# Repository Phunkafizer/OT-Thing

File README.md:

# OTthing

**A compact WiFi <-> OpenTherm (master & slave) interface**

## Project homepage

https://www.seegel-systeme.de/2025/01/05/ot-thing-das-universelle-wifi-opentherm-interface/

*OTthing board*

*OTthing wiring*

*OTthing web interface*

*Home Assistant integration*

## Overview

OTthing is a versatile OpenTherm gateway that connects your heating system to the Internet via WiFi. It acts as an OpenTherm master (controlling your boiler) and/or slave (integrating with room thermostats), providing real-time monitoring and control through a modern web interface and Home Assistant integration.

### Key Features

* **Dual OpenTherm Modes**: Operate as both an OpenTherm master and a slave simultaneously
* **Single-Board Compact Design**: Cost-efficient SMD-based single-board hardware with a small enclosure footprint
* **OpenTherm Compatibility**: Works with OpenTherm-compatible equipment that implements the functions supported by OTthing; available features vary by device
* **USB-C Powered**: Simple and reliable power supply through a standard USB-C connector
* **Web Dashboard**: Real-time status monitoring with system metrics
* **Home Assistant Integration**: Native MQTT discovery and seamless HA integration
* **Multi-Zone Support**: Control up to 2 heating circuits with independent parameters
* **Time Program**: Built-in scheduling for automatic heating setpoint changes
* **Heating Curve Control**: Outdoor-compensated flow temperature control with configurable curve parameters
* **Flow & Setpoint Management**: Fine-grained control for CH temperature targets, modes, and operating limits
* **Raw OpenTherm Tools**: Direct read/write request endpoint for diagnostics and advanced integrations
* **Real-Time Telemetry**: Live updates via WebSocket for logs and status changes
* **REST API**: Full HTTP interface for status, configuration, control commands, and topic discovery
* **WiFi Provisioning**: Built-in network scan and credential setup through the web interface
* **OTA Firmware Update**: In-browser firmware upload endpoint with automatic reboot on success
* **Local Data Export**: Device data and diagnostics export from the web UI for troubleshooting
* **External Inputs & Sensors**: Optional DS18B20, pulse input, or photointerrupter support (for example, condensate monitoring)
* **Selectable Operating Strategies**: Run OTthing as a full heating controller or in monitoring-first mode for telemetry-only operation
* **Automatic Bypass Behavior**: Allows you to restore conventional room-thermostat operation without rewiring
* **Failsafe Runtime Status**: Device health and communication state tracking for robust operation
* **Local Control**: Responsive web UI with no cloud dependency
* **Modular Design**: Extensible architecture supporting multiple integrations
* **Open-Source Platform**: Open hardware and firmware for custom extensions and modifications
* **Advanced Configuration**: Room modes (off/heat/auto), flow control, heating curves, and more
* **Detailed Logging**: Real-time log streaming to monitor system behavior
* **Turbo Mode**: Temporarily raises the flow target by a configurable amount and duration
* **Automatic Suspend**: Optional suspension based on outside temperature, room conditions, and minimum flow thresholds
* **Customizable dashboard**: add metrics to dashboard

## Architecture

The firmware consists of several functional modules:

* **OpenTherm Control** (`otcontrol.cpp`): Manages master/slave communication with the boiler
* **Master Requests** (`masterrequests.cpp`): Builds and schedules OpenTherm master requests and polling cycles
* **OpenTherm Values** (`otvalues.cpp`): Stores, normalizes, and exposes decoded OpenTherm data points
* **Heating Curve** (`heatingcurve.cpp`): Calculates the target flow temperature from heating-curve parameters
* **MQTT Integration** (`mqtt.cpp`): Publishes device state and subscribes to control topics
* **Device Status** (`devstatus.cpp`): Tracks runtime health, connectivity, and status flags
* **Auxiliary Input** (`auxInput.cpp`): Handles external input signals for additional control logic
* **Web Portal** (`portal.cpp`): Serves the responsive dashboard and API endpoints
* **Heating Control** (`CHcontrol.cpp`): Manages heating circuits, setpoints, and modes
* **Sensor Integration** (`sensors.cpp`): Collects data from external sensors
* **Configuration Management** (`devconfig.cpp`): Handles persistent device settings

## Hardware

* **MCU**: ESP32-C3 (or a compatible MCU with UART pins)
* **Communication**: OpenTherm interface
* **Power**: via USB
* **Optional**: DS18B20 1-Wire temperature sensors and auxiliary inputs

OpenTherm support and available controls depend on the boiler or other equipment. Check the device documentation and OTthing schematics before installation. Disconnect equipment from mains power before wiring; have boiler wiring performed by a qualified installer where required. Connect OpenTherm through the board's designated terminals, never directly to MCU GPIO pins.

## Installation & Setup

1. **Hardware Setup**:

   - Connect the OpenTherm slave side (boiler / ventilation / solar storage) to the **Boiler** screw terminal on OTthing
   - Optionally connect the room unit to the **Roomunit** screw terminals on OTthing
   - Connect OTthing to a USB-C power supply

2. **Access the Web Interface**:

   - The device creates a WiFi access point for provisioning or connects to its configured network
   - The default access point password is `12345678`; change it before deployment
   - Access the web UI at `http://<otthing-ip>/` (default: 4.3.2.1)

3. **Configure**:

   - Set your boiler type and heating circuit parameters
   - Configure the MQTT broker if you are using Home Assistant
   - Adjust setpoints, heating curves, and control modes

### Build and Flash (Developers)

Install PlatformIO, then run these commands from the `Firmware/` directory:

```bash
platformio run --environment release
platformio run --environment release --target upload
```

The first command builds the firmware. The next two upload the firmware and the LittleFS web assets; perform both uploads when installing a complete build. The firmware project reads access point SSID, password, and hostname from `default.ini` unless overridden by the build environment. Set a unique access point password before deploying devices.

## API Reference

OTthing exposes the following REST endpoints and WebSocket connection:

When web authentication is configured, protected endpoints require a valid login session. Requests without a valid session return 401; log in through the web UI before using these endpoints.

### Core Status Endpoints

* **`GET /`** - Web dashboard (HTML)
* **`GET /status`** - Current device and boiler status (JSON)
* **`GET /config`** - Device configuration and settings (JSON)
* **`POST /config`** - Update device configuration (JSON body)
* **`GET /otitems`** - Raw OpenTherm items and values from master and slave (JSON)
* **`GET /topics`** - List all available MQTT control topics (text/plain)

### Control Endpoints

* **`GET /set?key=value`** - Update settings via query parameters
  - Examples: `/set?chSetTemp1=50`, `/set?chMode1=heat`
  - Use `/topics` to discover supported control keys. URL-encode values when they contain reserved characters.
  - Returns 200 on success, 503 if the value cannot be set

* **`GET /slaverequest?id=X&rw=Y&data=HEX`** - Send a raw OpenTherm slave request
  - `id`: OpenTherm message ID (integer)
  - `rw`: 1 for READ_DATA, 0 for WRITE_DATA
  - `data`: Hex-encoded data value
  - Returns JSON with response type, ID, and data

### System Endpoints

* **`GET /scan`** - Scan for available WiFi networks
  - Returns JSON with the SSID, RSSI, and channel for each network
  - Status field: -2 (scanning in progress), -1 (failed), 0+ (number of networks found)

* **`POST /setwifi`** - Configure WiFi credentials
  - Parameters: `ssid` and `pass` (URL-encoded)
  - Triggers a device reboot and a WiFi connection attempt

* **`GET /reboot`** - Trigger a device reboot
  - Returns 200 and schedules a reboot

* **`POST /update`** - Firmware update (binary upload)
  - Returns 200 on success, 500/503 on error
  - Triggers an automatic reboot if the update succeeds

### Real-time Communication

* **`WebSocket /ws`** - Real-time updates and log streaming
  - Receives log messages and status updates
  - Can be used to monitor device behavior in real time

## Testing & Development

A Python mock server is included for local UI and API testing. Install its dependencies and start it from the `Firmware/` directory:

```bash
python -m pip install -r requirements.txt
python tools/mock_otthing.py
```

The server listens on `http://127.0.0.1:8081/`. It is useful for UI development and API integration, but it does not replace testing against physical OpenTherm hardware.

### MQTT Notes

The device subscribes to control topics under `otthing/<device-id>/<key>/set`; `/topics` lists the supported keys. Home Assistant discovery is provided through MQTT when a broker is configured.

Changes sent through the web API are also published to the corresponding MQTT `/set` topic as retained messages. A broker can replay retained commands when the device reconnects, including after a reboot. Keep this in mind for temporary controls such as Turbo mode, and clear any stale retained command from the broker when needed.

### Troubleshooting

* **Cannot reach the web UI**: Confirm the phone or computer is connected to the OTthing access point or the same network as the device, then check the device IP.
* **No OpenTherm communication**: Check the board terminals, wiring polarity where applicable, boiler compatibility, and the device's status and logs.
* **Home Assistant entities are missing**: Confirm broker connectivity and MQTT discovery settings, then review device logs and the broker's topics.
* **A setting returns 401**: Log in through the web UI and retry the request with the browser session.
* **A temporary action returns after reboot**: Check whether a retained MQTT `/set` command is replaying it.

## Schematics

## Discussion

https://community.home-assistant.io/t/ot-thing-an-opentherm-wifi-gateway-with-integrated-ot-master-slave/824667

## Reporting issues

When reporting issues, please supply:

* Brand and model of the boiler and room unit
* OTthing firmware version and the steps that reproduce the issue
* expected behaviour
* Log
* Status JSON
* Configuration JSON
* OT items JSON
* Data history JSON

All of this data can be exported from the OTthing using the export function at the bottom of the web UI.
Only one concern per issue!

## Contributing

* Make changes in a new branch based on the [`develop`](../../tree/develop) branch.
* Address only one issue per PR.
* Create the PR against the [`develop`](../../tree/develop) branch.

## Known Working Devices

Below is an excerpt of hardware devices reported to work successfully with **OTthing**. If you have verified additional devices, contributions and reports are very welcome!

### Boilers, heatpumps, heating systems, ventilation systems
* **ACV** compact HRE eco 18 solo
* **De Dietrich** Inidens 20/24 MI
* **De Dietrich** MCR 24 Home
* **De Dietrich** MPX 24/29 MI Compact
* **Domusa** BioClass HM 16 (Pellet)
* **Elco** Trigon S 
* **Hoval** TopGas
* **Ideal** Logic Max combi
* **Immergas** Victrix Tera 24 Plus
* **Intergas** Kombi Kompakt HRE 36/30 A
* **Intergas** Xtreme 36
* **Intergas** HRE 36/30A
* **Junkers** Cerasmart ZSB 3-16 *(with OpenTherm module OTM 1)*
* **Lamborghini** IX Condens 25 C
* **MHG**
* **Remeha** Elga Ace
* **Remeha** Tzerra 28c
* **Remeha** Tzerra Ace
* **Termet** Gold Plus 2
* **Viadrus** K4 (e-board SIT 7530197_01)
* **Viessmann** Vitodens 100-W (B1KG)
* **Weheat** Sparrow P60
* **Westen** Boyler Digit+
* **Windhager** BioWin (Pellet)

### Roomunits, thermostats, others
* **Baxi** RC 06.20
* **De Dietrich** AD304
* **De Dietrich** iSense (AD289)
* **Evohome** R8810 bridge
* **Google** Nest Thermostat E
* **Honeywell** DT4M
* **Hoval** RS-OT
* **Immergas** CAR V2
* **Intergas** Comfort Touch
* **Junkers** TF 30
* **MHG** Ceta 107
* **REMEHA** iSense
* **Siemens** QAA73
* **TADO** Thermostat X
* **Theben / Windhager** RAM 786

---
*Feel free to open a Pull Request or issue to report additional compatible devices!*

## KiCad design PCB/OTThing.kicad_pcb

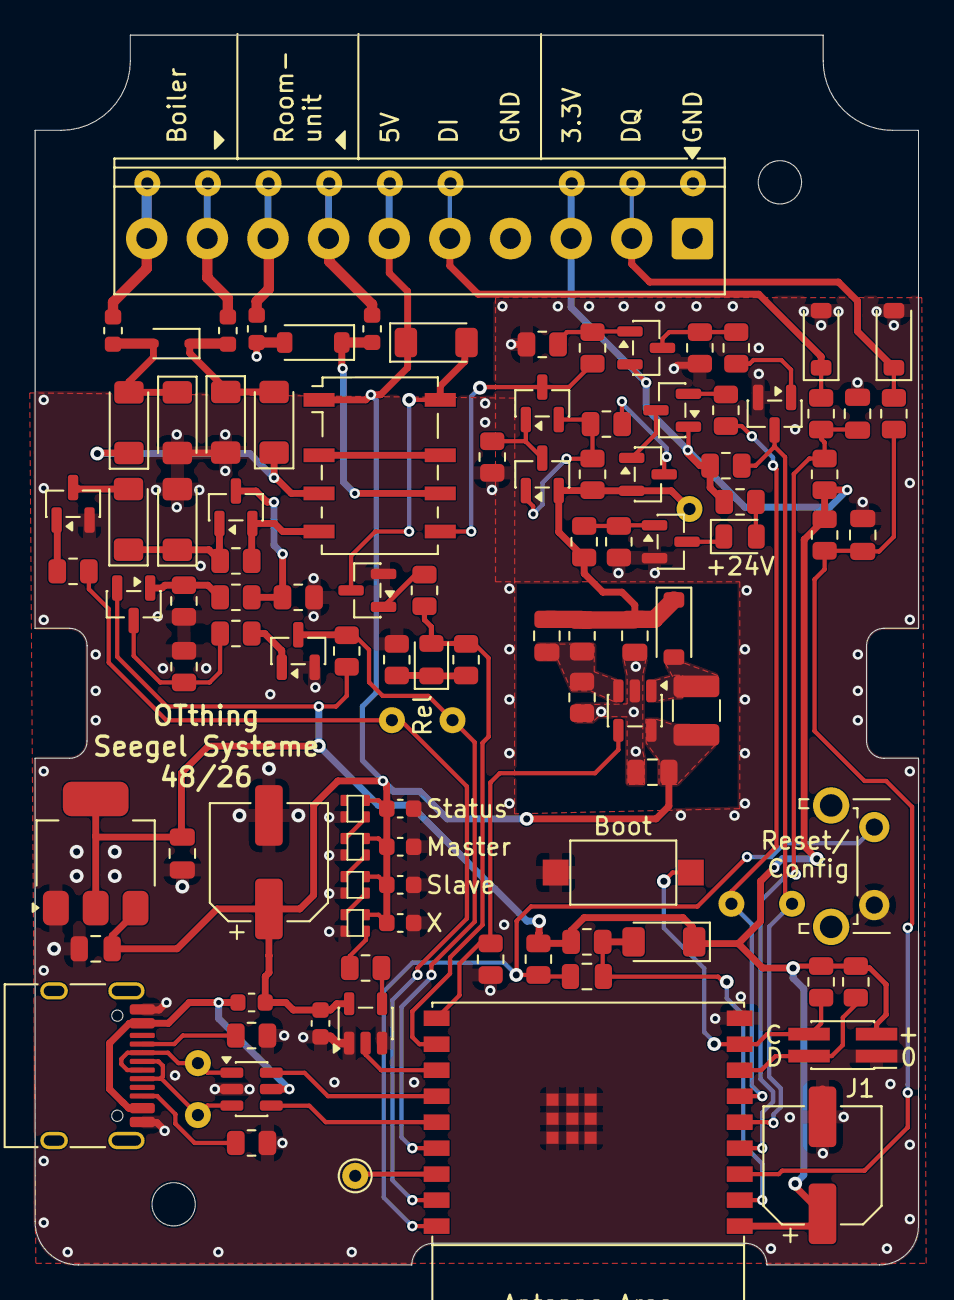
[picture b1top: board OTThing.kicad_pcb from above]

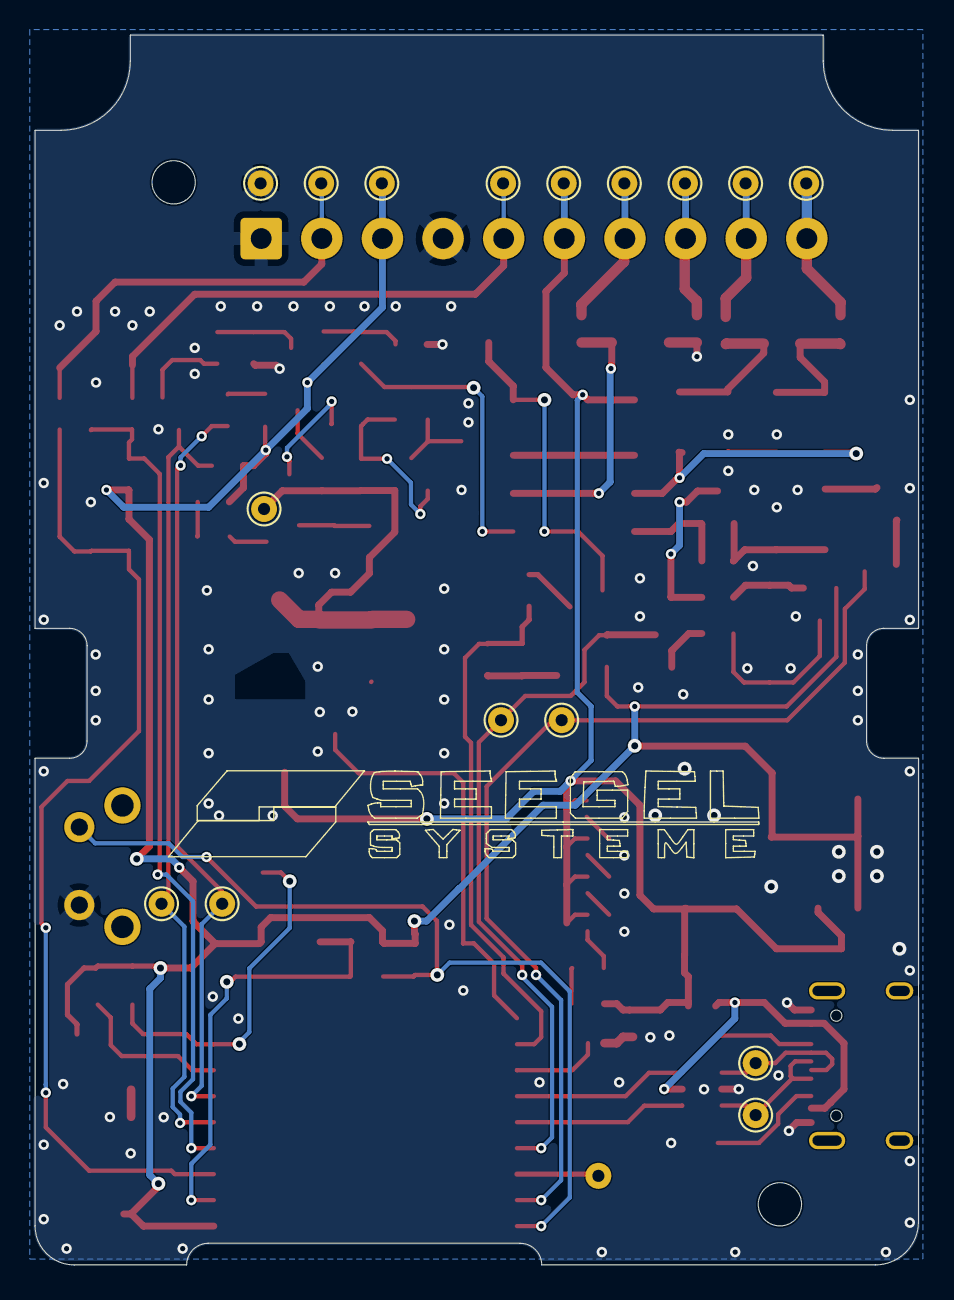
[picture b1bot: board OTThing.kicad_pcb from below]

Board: 2 copper layers, 51.0 x 71.0 mm, 119 parts (16 on the bottom side), 66 nets.

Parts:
C1, C3: 470pF; C_0805_2012Metric
C2, C4, C5: 10µ; C_0805_2012Metric
C6: 100µ; CP_Elec_6.3x5.4
C7, C9: 4µ7; C_0805_2012Metric
C8: 22pF; C_0805_2012Metric
C10: 470µ; CP_Elec_6.3x7.7
C11, C12, C13, C14, C15: 100n; C_0603_1608Metric
D1: ZMM4V3; D_MiniMELF
D2: ZMM15; D_MiniMELF
D3, D17: PTVS3V3S1UR,115; D_SOD-123
D4, D5, D6, D7, D8, D18: LL4148; D_MiniMELF
D9: MBR0540; D_SOD-123
D12, D14: YL; LED_0805_2012Metric
D15: PESD24VL1BA; D_SOD-323
D16: PTVS24VS1UR; D_SOD-123
FB1, FB2, FB3, FB4, FB5: L_0603_1608Metric
H1, H2: MountingHole; MountingHole_2.5mm
IC1: TPS61041; SOT-23-5
J1: Conn_01x04; PinHeader_2x02_P1.27mm_Vertical_SMD
J3: USB_C_Receptacle_USB2.0; USB_C_Receptacle_HRO_TYPE-C-31-M-12
J4: TerminalBlock_Phoenix_PT-1,5-10-3.5-H_1x10_P3.50mm_Horizont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
K1: G6K-2F-Y-5V; Relay_DPDT_Omron_G6K-2F-Y
L1: 10µ; L_1210_3225Metric
LED1, LED2, LED3, LED4: XL-1615RGBC-WS2812B-S
Q1, Q4, Q5, Q6, Q7, Q11: BC857C; SOT-23
Q2, Q8, Q9, Q10, Q12, Q13: BC847C; SOT-23
R1, R4, R29, R30, R31, R36, R38, R39, R40: 4k7; R_0805_2012Metric
R2, R6: 120; R_0805_2012Metric
R3: 18k; R_0805_2012Metric
R5: 470; R_0805_2012Metric
R7, R22, R33: 330; R_0805_2012Metric
R8, R9: 5k1; R_0805_2012Metric
R12, R14, R23, R26, R34: 3k3; R_0805_2012Metric
R13, R21, R27: 33k; R_0805_2012Metric
R15, R25, R28: 12k; R_0805_2012Metric
R16: 220k; R_0805_2012Metric
R17: 6k8; R_0805_2012Metric
R18: 22k; R_0805_2012Metric
R19: 39; R_0805_2012Metric
R20, R24: 100; R_0805_2012Metric
R32: 1k; R_0805_2012Metric
R37: 10k; R_0805_2012Metric
SW1: RST/CONFIG; SW_Tactile_SPST_Angled_PTS645Vx83-2LFS
SW2: BOOT; SW_SPST_CK_RS282G05A3
TP1, TP2, TP3, TP4, TP5, TP6, TP7, TP8, TP9, TP10, TP11, TP12, TP13, TP14, TP15, TP16, TP17: TestPoint_THTPad_D1.5mm_Drill0.7mm
U1: ESP32-C3-WROOM-02
U2: 74AHCT1G125; SOT-23-5
U5: USBLC6-2SC6; SOT-23-6
U6: AMS1117-3.3; SOT-223-3_TabPin2

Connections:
+3.3V: C4.1, C6.1, D8.1 (K), J1.3, J4.3, Q2.1 (B), Q7.2 (E), Q11.2 (E), R2.2, R12.2, R13.2, R14.2, R23.2, R26.2, R31.2, R34.2, R38.2, TP3.1 (1_1), U1.1 (3V3), U6.2 (VO)
+5V: C2.1, C7.1, C10.1, C11.1, C12.1, C13.1, C14.1, C15.1, D18.1 (K), FB5.2, IC1.5 (VIN), J4.6, K1.1, L1.1, LED1.3 (VDD), LED2.3 (VDD), LED3.3 (VDD), LED4.3 (VDD), TP5.1 (1_1), U2.5 (VCC), U6.3 (VI)
+24V: C8.1, C9.1, D9.1 (K), Q4.2 (E), Q6.2 (E), R16.1, R20.2, R27.2, TP10.1 (1_1)
+VBUS: FB5.1, J3.A4 (VBUS), J3.A9 (VBUS), J3.B4 (VBUS), J3.B9 (VBUS), U5.5 (VBUS)
/CFG: C5.2, R12.1, SW1.1, U1.18 (GPIO0/ADC1_CH0/XTAL_32K_P)
/DI: D17.1 (K), J4.5, R22.1, TP4.1 (1_1)
/EN: C5.1, D8.2 (A), R13.1, U1.2 (EN/CHIP_PU)
/EN24: IC1.4 (EN), R28.1, U1.10 (GPIO10)
/LEDs/DATA: U1.12 (GPIO21/U0TXD), U2.2
/OTM_RX: Q10.3 (C), R38.1, TP12.1 (1_1), U1.15 (GPIO3/ADC1_CH3)
/OTS_RX: Q8.3 (C), R31.1, TP14.1 (1_1), U1.5 (GPIO6)
/OTS_TX: R1.2, TP13.1 (1_1), U1.6 (GPIO7)
/OpenTherm interface/OTMASTER_A: FB3.2, J4.10, TP9.1 (1_1)
/OpenTherm interface/OTMASTER_B: FB4.2, J4.9, TP8.1 (1_1)
/OpenTherm interface/OTSLAVE_A: FB1.2, J4.8, TP7.1 (1_1)
/OpenTherm interface/OTSLAVE_B: FB2.2, J4.7, TP6.1 (1_1)
/REL: D12.2 (A), R4.2, R25.1, U1.11 (GPIO20/U0RXD)
/USBCDM: J3.A7 (D-), J3.B7 (D-), TP16.1 (1_1), U5.1 (I/O1)
/USBCDP: J3.A6 (D+), J3.B6 (D+), TP15.1 (1_1), U5.3 (I/O2)
GND: C1.2, C2.2, C3.2, C4.2, C6.2, C7.2, C9.2, C10.2, C11.2, C12.2, C13.2, C14.2, C15.2, D2.2 (A), D3.2 (A), D5.2 (A), D7.2 (A), D16.2 (A), D17.2 (A), FB1.1, IC1.2 (GND), J1.1, J3.A1 (GND), J3.A12 (GND), J3.B1 (GND), J3.B12 (GND), J4.1, J4.4, LED1.1 (VSS), LED2.1 (VSS), LED3.1 (VSS), LED4.1 (VSS), Q8.2 (E), Q9.2 (E), Q10.2 (E), Q12.2 (E), Q13.2 (E), R3.1, R6.1, R7.2, R8.2, R9.2, R15.2, R17.2, R21.1, R28.2, R29.2, R32.1, R40.2, SW1.2, SW2.2, TP1.1 (1_1), U1.9 (GND), U1.19 (GND), U2.1, U2.3 (GND), U5.2 (GND), U6.1 (GND)
unnamed: D1.2 (A), Q9.3 (C)
unnamed: D1.1 (K), D2.1 (K), Q1.1 (B), R5.2
unnamed: D3.1 (K), J4.2, R33.1, TP2.1 (1_1)
unnamed: D4.1 (K), D6.1 (K), K1.3
unnamed: D9.2 (A), IC1.1 (SW), L1.2
unnamed: D12.1 (K), R6.2, R25.2
unnamed: D14.2 (A), R2.1
unnamed: D14.1 (K), Q13.3 (C)
unnamed: D6.2 (A), D7.1 (K), D15.1 (A1), FB4.1
unnamed: D4.2 (A), D5.1 (K), D15.2 (A2), FB3.1
unnamed: D16.1 (K), FB2.1, K1.6
unnamed: D18.2 (A), K1.8, Q12.3 (C)
unnamed: C8.2, IC1.3 (FB), R15.1, R16.2
unnamed: J1.2, R34.1, U1.7 (GPIO8)
unnamed: J1.4, R26.1, SW2.1, U1.8 (GPIO9)
unnamed: J3.A5 (CC1), R9.1
unnamed: J3.B5 (CC2), R8.1
unnamed: K1.2, K1.7
unnamed: LED1.2 (DIN), R24.1
unnamed: LED1.4 (DOUT), LED2.2 (DIN)
unnamed: LED2.4 (DOUT), LED3.2 (DIN)
unnamed: LED3.4 (DOUT), LED4.2 (DIN)
unnamed: Q1.3 (C), R7.1, R37.1
unnamed: K1.4, Q1.2 (E), R5.1
unnamed: Q2.3 (C), Q4.1 (B)
unnamed: Q2.2 (E), R1.1
unnamed: Q4.3 (C), R19.2
unnamed: Q5.1 (B), Q6.3 (C), R21.2
unnamed: K1.5, Q5.3 (C), R18.2
unnamed: Q5.2 (E), Q6.1 (B), R19.1, R20.1
unnamed: Q7.1 (B), R17.1, R18.1
unnamed: Q7.3 (C), R29.1, R30.2
unnamed: Q8.1 (B), R30.1
unnamed: Q9.1 (B), R36.1
unnamed: Q10.1 (B), R39.1
unnamed: Q11.1 (B), R3.2, R37.2
unnamed: Q11.3 (C), R39.2, R40.1
unnamed: Q12.1 (B), R4.1
unnamed: Q13.1 (B), R27.1, R32.2
unnamed: R24.2, U2.4
unnamed: TP17.1 (1_1), U1.16 (GPIO2/ADC1_CH2)
unnamed: C1.1, R14.1, R33.2, U1.3 (GPIO4/ADC1_CH4)
unnamed: C3.1, R22.2, R23.1, U1.4 (GPIO5/ADC2_CH0)
OTM_TX: R36.2, TP11.1 (1_1), U1.17 (GPIO1/ADC1_CH1/XTAL_32K_N)
USBDM: U1.13 (GPIO18/USB_D-), U5.6 (I/O1)
USBDP: U1.14 (GPIO19/USB_D+), U5.4 (I/O2)

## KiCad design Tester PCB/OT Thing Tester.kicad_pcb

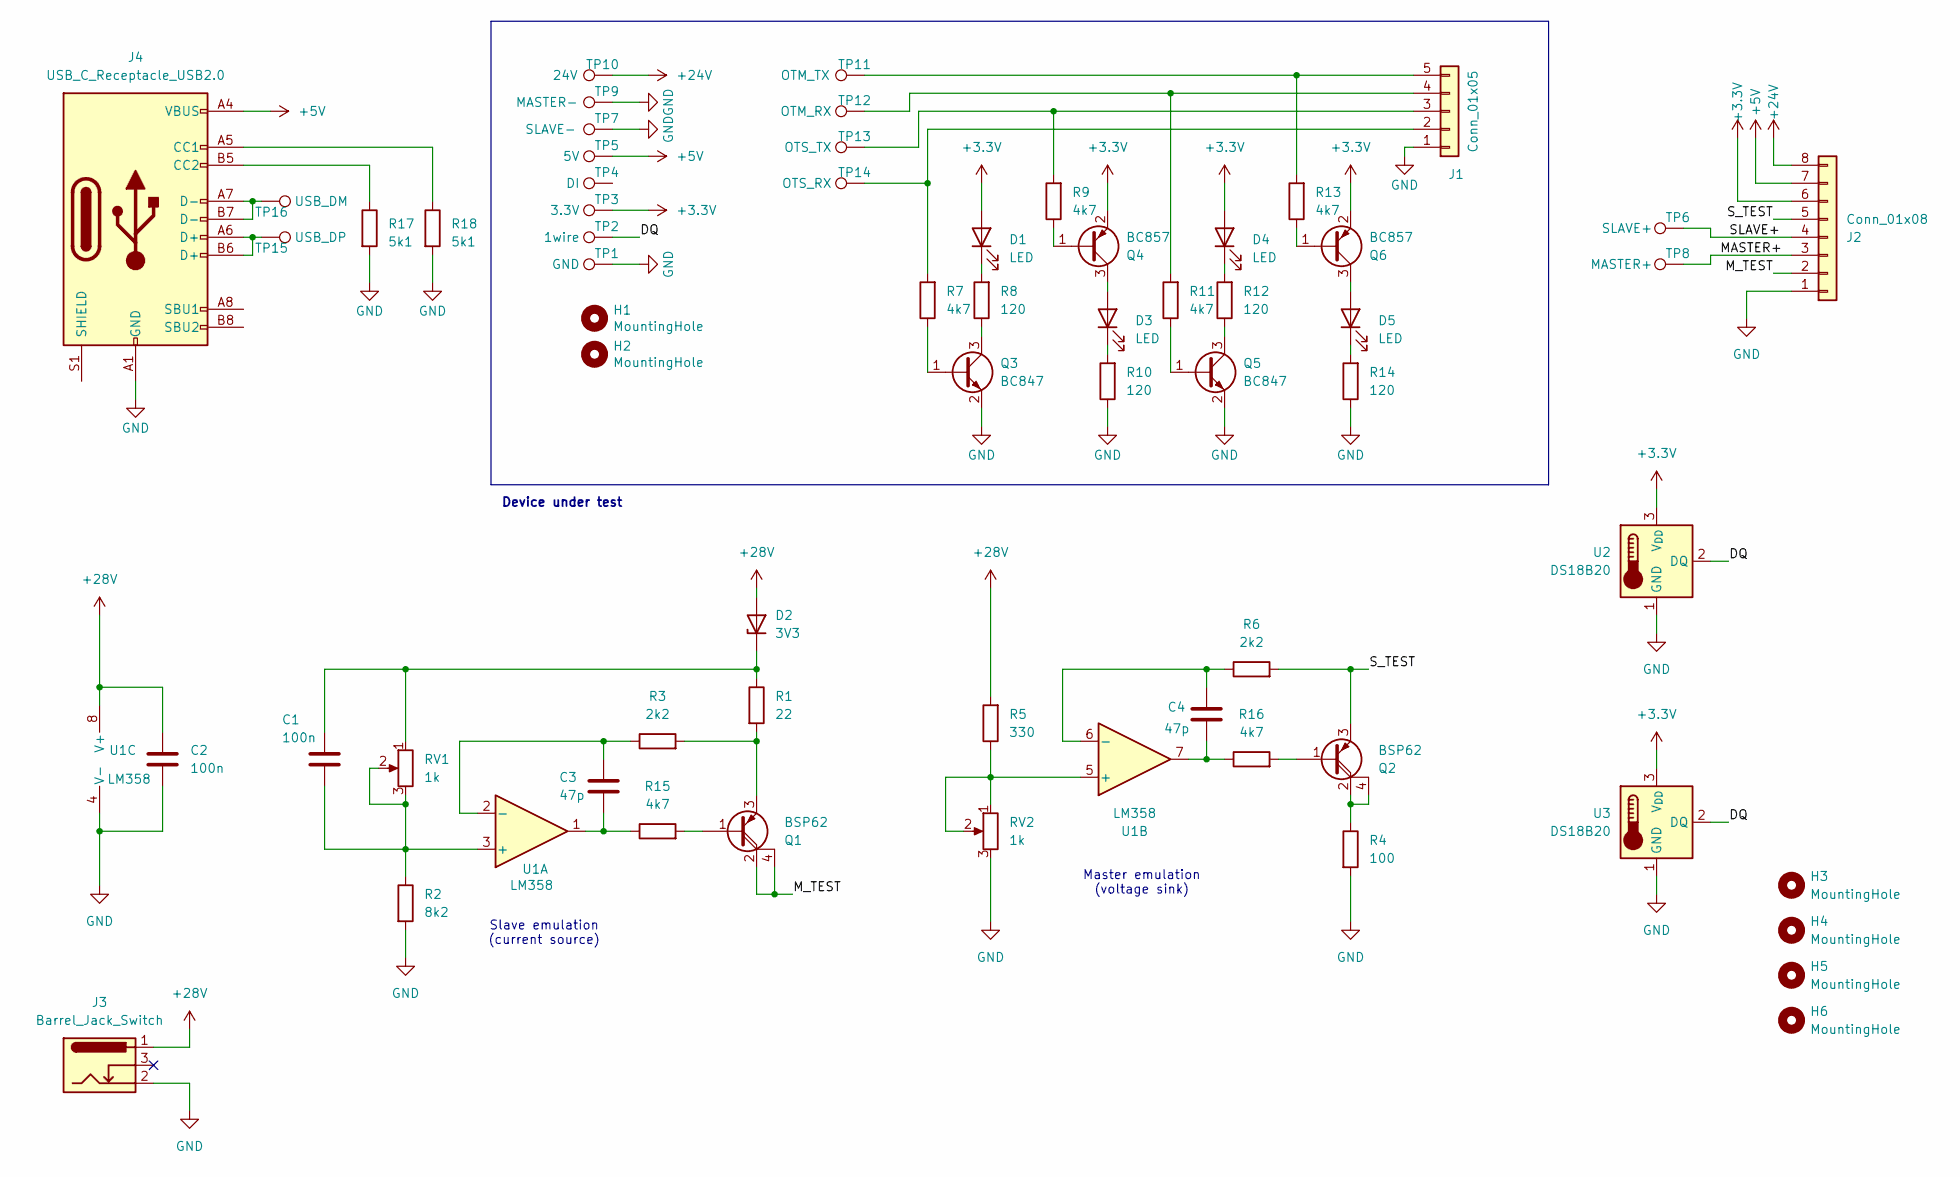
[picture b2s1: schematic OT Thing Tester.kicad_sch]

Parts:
C1, C2: 100n; C_0805_2012Metric
C3, C4: 47p; C_0805_2012Metric
D1, D3, D4, D5: LED; LED_0805_2012Metric
D2: 3V3; D_MiniMELF
H1, H2: MountingHole; MountingHole_2.7mm_M2.5
H3, H4, H5, H6: MountingHole; MountingHole_3.2mm_M3_DIN965_Pad
J1: Conn_01x05; PinHeader_1x05_P2.54mm_Vertical
J2: Conn_01x08; PinHeader_1x08_P2.54mm_Vertical
J3: Barrel_Jack_Switch; BarrelJack_GCT_DCJ200-10-A_Horizontal
J4: USB_C_Receptacle_USB2.0; USB_C_Receptacle_HRO_TYPE-C-31-M-12; LCSC C2927038
Q1, Q2: BSP62; SOT-223
Q3, Q5: BC847; SOT-23
Q4, Q6: BC857; SOT-23
R1: 22; R_0805_2012Metric
R2: 8k2; R_0805_2012Metric
R3, R6: 2k2; R_0805_2012Metric
R4: 100; R_0805_2012Metric
R5: 330; R_0805_2012Metric
R7, R9, R11, R13, R15, R16: 4k7; R_0805_2012Metric
R8, R10, R12, R14: 120; R_0805_2012Metric
R17, R18: 5k1; R_0805_2012Metric; LCSC C118848
RV1, RV2: 1k; Potentiometer_Piher_PT-6-V_Vertical
TP1: GND; TestPoint_THTPad_D2.0mm_Drill1.1mm
TP2: 1wire; TestPoint_THTPad_D2.0mm_Drill1.1mm
TP3: 3.3V; TestPoint_THTPad_D2.0mm_Drill1.1mm
TP4: DI; TestPoint_THTPad_D2.0mm_Drill1.1mm
TP5: 5V; TestPoint_THTPad_D2.0mm_Drill1.1mm
TP6: SLAVE+; TestPoint_THTPad_D2.0mm_Drill1.1mm
TP7: SLAVE-; TestPoint_THTPad_D2.0mm_Drill1.1mm
TP8: MASTER+; TestPoint_THTPad_D2.0mm_Drill1.1mm
TP9: MASTER-; TestPoint_THTPad_D2.0mm_Drill1.1mm
TP10: 24V; TestPoint_THTPad_D2.0mm_Drill1.1mm
TP11: OTM_TX; TestPoint_THTPad_D2.0mm_Drill1.1mm
TP12: OTM_RX; TestPoint_THTPad_D2.0mm_Drill1.1mm
TP13: OTS_TX; TestPoint_THTPad_D2.0mm_Drill1.1mm
TP14: OTS_RX; TestPoint_THTPad_D2.0mm_Drill1.1mm
TP15: USB_DP; TestPoint_THTPad_D2.0mm_Drill1.1mm
TP16: USB_DM; TestPoint_THTPad_D2.0mm_Drill1.1mm
U1: LM358; SO-8_3.9x4.9mm_P1.27mm
U2, U3: DS18B20; TO-92_Inline

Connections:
+3.3V: D1.2 (A), D4.2 (A), J2.6, Q4.2 (E), Q6.2 (E), TP3.1 (1_1), U2.3 (V_{DD}), U3.3 (V_{DD})
+5V: J2.7, J4.A4 (VBUS), J4.A9 (VBUS), J4.B4 (VBUS), J4.B9 (VBUS), TP5.1 (1_1)
+24V: J2.8, TP10.1 (1_1)
+28V: C2.1, D2.2 (A), J3.1, R5.2, U1.8 (V+)
/DQ: TP2.1 (1_1), U2.2 (DQ), U3.2 (DQ)
/MASTER+: J2.3, TP8.1 (1_1)
/M_TEST: J2.2, Q1.2 (C), Q1.4 (C)
/SLAVE+: J2.4, TP6.1 (1_1)
/S_TEST: J2.5, Q2.3 (E), R6.2
unnamed: C3.2, R15.1, U1.1
unnamed: C4.2, R16.1, U1.7
unnamed: D1.1 (K), R8.2
unnamed: C1.2, D2.1 (K), R1.1, RV1.1
unnamed: D3.2 (A), Q4.3 (C)
unnamed: D3.1 (K), R10.2
unnamed: D4.1 (K), R12.2
unnamed: D5.2 (A), Q6.3 (C)
unnamed: D5.1 (K), R14.2
unnamed: J1.2, R7.2, TP14.1 (1_1)
unnamed: J1.3, R9.2, TP13.1 (1_1)
unnamed: J1.4, R11.2, TP12.1 (1_1)
unnamed: J1.5, R13.2, TP11.1 (1_1)
unnamed: J4.A5 (CC1), R18.1
unnamed: J4.B5 (CC2), R17.1
unnamed: J4.A6 (D+), J4.B6 (D+), TP15.1 (1_1)
unnamed: J4.A7 (D-), J4.B7 (D-), TP16.1 (1_1)
unnamed: Q1.1 (B), R15.2
unnamed: Q1.3 (E), R1.2, R3.2
unnamed: Q2.1 (B), R16.2
unnamed: Q2.2 (C), Q2.4 (C), R4.1
unnamed: Q3.1 (B), R7.1
unnamed: Q3.3 (C), R8.1
unnamed: Q4.1 (B), R9.1
unnamed: Q5.1 (B), R11.1
unnamed: Q5.3 (C), R12.1
unnamed: Q6.1 (B), R13.1
unnamed: C1.1, R2.1, RV1.2, RV1.3, U1.3 (+)
unnamed: C3.1, R3.1, U1.2 (-)
unnamed: C4.1, R6.1, U1.6 (-)

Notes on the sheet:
Master emulation (voltage sink)
Slave emulation (current source)
Device under test

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
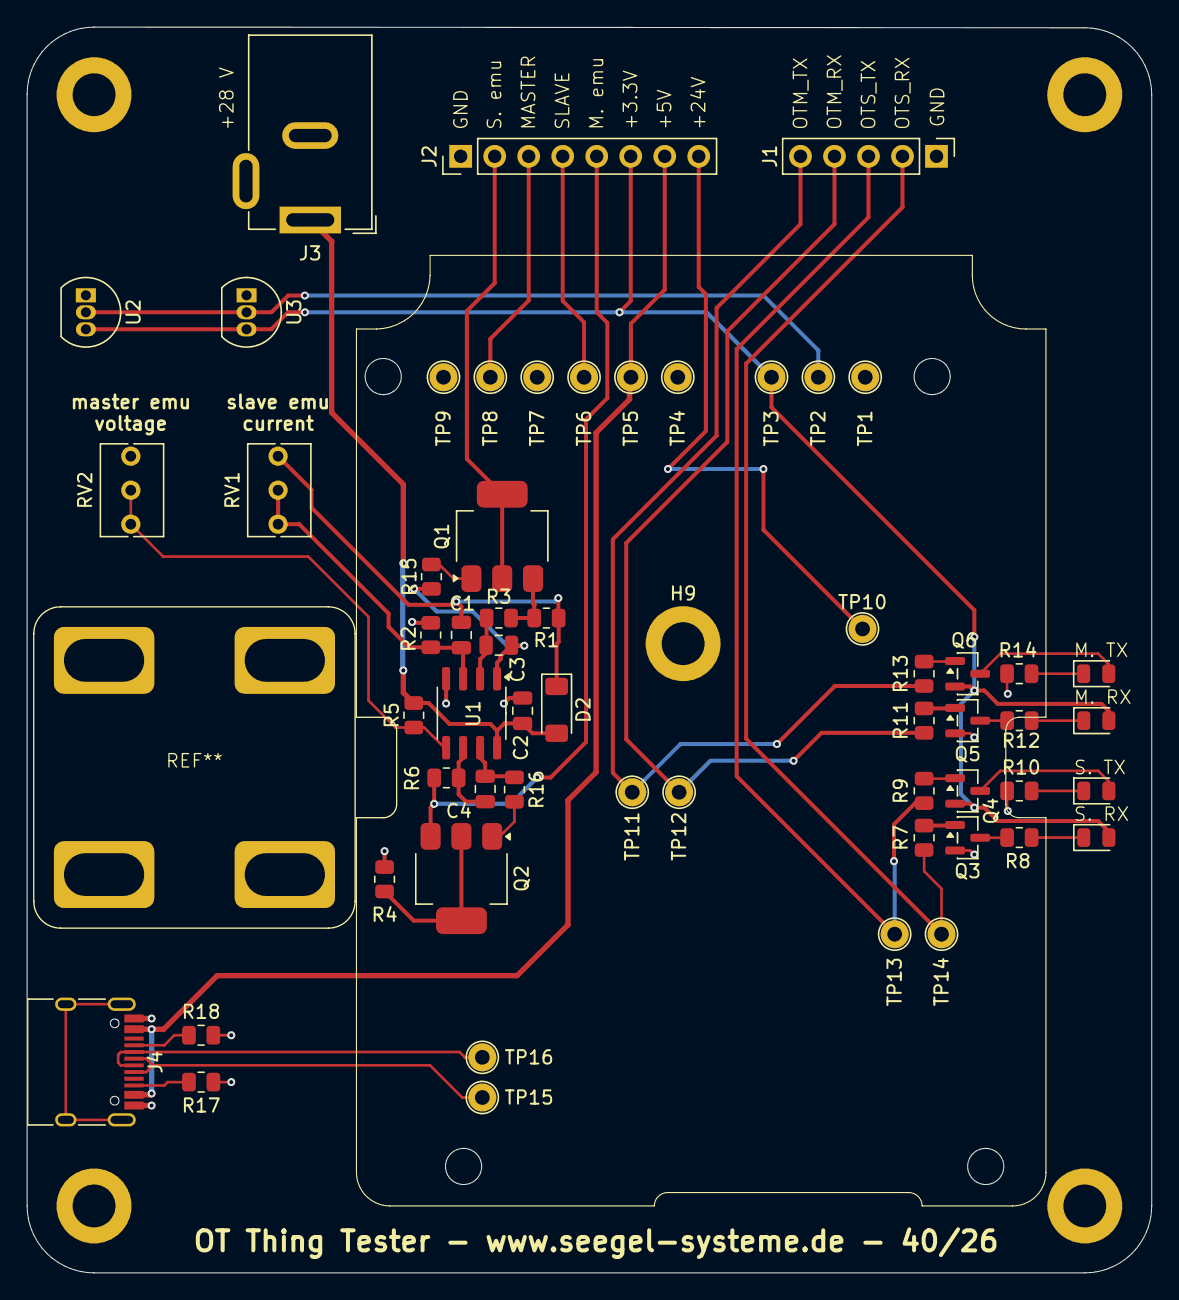
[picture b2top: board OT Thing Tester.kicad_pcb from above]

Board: 2 copper layers, 84.0 x 93.0 mm, 67 parts (0 on the bottom side), 41 nets.

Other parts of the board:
H7, H8: MountingHole; MountingHole_2.7mm_M2.5
H9: MountingHole; MountingHole_3.2mm_M3_DIN965_Pad

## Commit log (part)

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2024-09-09 change MCU redesign OT interfaces
2024-10-14 Change MCU
2024-11-04 Migrate to ESP32
2024-11-05 finish 45/24
2025-01-08 add pullups for stability
2025-01-08 Home Assistant Discovery
    OpenTherm timer TX
    WiFi client for openweather
    OT loopback test
2025-01-09 add factory reset
    select OT mode from webUI
    OT loopback tests
2025-01-13 add HA climate for dhw
    calc flowtemp from outsidetemp
2025-01-13 add LED for +24V enable
2025-01-19 refactoring cleanup add more OT values show message type in log
2025-01-22 refactoring RX TX LEDs in master mode
2025-01-23 add repeater mode add master status
2025-01-23 remove test delays add txcounter for repeatermode
2025-01-31 add timeoutcounter add remote boiler flags improve outside temp logic
2025-02-01 boiler's sensor for outside temperature fix TX counter
2025-03-02 Add runtime & more fields Add roomtemperature compensation Asynchronous http client
2025-03-27 migrate to pioarduino smart power add more OT values new partitiontable
2025-03-28 Migrate to KiCad 9.0
2025-03-28 fix .gitignore
2025-03-28 add Test PCB
2025-03-28 clean up add reset reason to status fix typos
2025-03-28 fix typos & translations
2025-03-29 increase app partition size autoscroll button add OT val room override
2025-03-30 fix update progress bar remove repeater mode remove debug outputs
2025-03-31 rename gateway -> repeater fix delay
2025-07-18 fix mqtt payload string fix OT repeater, forwarding unknown frames add interpreter for OT value remote specific flags
2025-07-28 fix fault flags
2025-09-03 Configure 1wire sensors for roomtemperature
2025-09-05 HA discovery for 1wire sensors
2025-09-07 Send autodiscovery for Toutside, DHWFlowRate & OpenThermVersionSlave
2025-09-14 refactoring fix translation
2025-09-15 add TrOverride2, RemoteOverrideFunction
2025-09-20 add some additional OT values to webUI add stub for scheduler in webUI refactoring string constats
2025-09-21 overriding values in repeater mode
2025-09-22 clean up
2025-09-24 refresh heat curve when changing default room set point for flow temp when chaning room set point show smartpowerenabled flag auto CI
2025-09-24 update build yaml
2025-09-24 update helper scripts
2025-09-24 auto CI remove calling helper
2025-09-24 fix platformio.ini
2025-09-24 add opentherm to libs
2025-09-25 add USB test points single board test w/ power supply
2025-09-30 add support for ventilation
2025-10-05 add vent versions to webUI write room temp & room set point as master API endpoint for slave request
2025-10-19 set overriding in repeater mode via MQTT refactoring
2025-10-19 fix translations
2025-10-20 log MQTT disconnection
2025-10-21 release
2025-10-23 automatically find com port
2025-10-23 add 3d model
2025-11-01 release fix slaveEnable in mastermode
2025-11-12 add OTC, summer mode & DHW blocking for boiler auto selection for roomsetpoint source round 1wire values
2025-11-16 configurable hostname display num WiFi & MQTT disconnects configurable MQTT keep alive
2025-11-17 configurable prefix for HA discovery
2025-11-18 add status USB CDC connect to webUI add OT field OEM diagnostic code fix mqtt disconnection counter add HA discovery flags for master status add HA discovery flags for slave status add HA discovery f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
2025-11-18 fix override in master mode with slave add mod & override to status
2025-11-19 Add HA discovery for max. capacity & min. modulation Add HA discovery for DHW bounds Add HA discovery for CH bounds
2025-11-20 option for 1wire outside temperature
2025-11-22 send outside temp to boiler fix outside temp < 0
2025-11-27 add roomsettemp to marker table, fix HA discovery
2025-11-28 new production
2025-11-28 remove object_id in HA discovery
2025-11-28 Show result message from openweather
2025-12-02 add license
2025-12-04 disable WiFi sleep reconnect WiFi on disconnect
2025-12-07 add OT value boiler heat exchanger temp add OT value boiler fan speed add OT value flame current fix ventilation fan speed refactoring
2025-12-11 configurable HA device name
2025-12-14 add timezone setting send datetime to roomunit fix sensor paths add image in README
2025-12-15 update from github via webUI 1wire: read immediately after scan
2025-12-18 fix MQTT control for DHW & CH2
2025-12-22 Update default.ini for otgw32
2025-12-25 PI controller for room compensation
2025-12-25 fix FW check
2025-12-26 CH suspend on reaching room setpoint
2026-01-04 icons for bool values hide controls not present in boiler show suspended state
2026-01-05 add switches for enabling room compensation add controls for setting max. modulation
2026-01-06 boost for room compensation
2026-01-08 calculate burner flame ratio & toggle frequency add OT fields CH pump operating hours & DHW pump operating hours save space on heating curve canvas show arrow in heating curve canvas for current flow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
2026-01-11 add slave (service) requests show reset reason in webUI add watchdog
2026-01-14 add note for issues
2026-01-15 static JSON buffer for status semaphore for device status fix suspend
2026-01-20 Set PI controller with room climate control add HA sensor for room setpoint fix synchronization
2026-01-20 read brand, brand version & brand serial from slave fix warnings
2026-01-22 fix HA warnings fix GCC warnings refactoring discoveries fix deviceclass "opening"
2026-01-22 remove orphan HA values fix update from github
2026-01-23 send master product & OT version
2026-01-23 inc version
2026-01-23 add OT values DHW burner starts & DHW pump starts fix typo remove override controls if caps not present
2026-01-23 fix typo
2026-01-24 calculate burner flame ratio & toggle frequency add OT fields CH pump operating hours & DHW pump operating hours save space on heating curve canvas show arrow in heating curve canvas for current flow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
2026-01-25 show slave features
2026-01-25 show rp_flags in webUI
2026-01-25 add sensor for current room temperature fix hiding CH2 controls
2026-01-25 fix stats for brand infos
2026-01-25 fix flag "smart power implemented"
2026-01-25 fix GCC warning
2026-01-25 read size of fault history buffer (FHB) read size of slave transparent parameters (TSPs) read power cycles
2026-01-27 add otitems to README
2026-01-29 add save log button
2026-01-29 fix reading brand values
2026-01-31 show basetopic on webUI status endpoint /topics
2026-02-02 increase range for gradient & offset compensate setpoint jumps in integrator
2026-02-05 HA: add device class and unit to number entities
2026-02-05 add blueprint
2026-02-05 fix blueprints
2026-02-09 Fix ERCs, DRCs & BOM
2026-02-11 fix unit for boiler fan speed sensor
2026-02-17 add 4 point curve
    add class for math logic
    add class for math logic
    add mapping
    add smooth steps
    fix offset
    fix debug compile
2026-02-17 hide DHW / CH2 fields when not installed
2026-02-17 clean up move strings to flash remove HA name setting
2026-02-17 show master's outside temp on WRITE catch & log invalid messages
2026-02-18 fixed linear curve and edit fields for 4 point curves
2026-02-21 update flow imediately when changing room compensation via MQtt
2026-02-22 update libraries, fix DRCs
2026-03-10 add parameter for min. flow temperatur configurable inputs (1wire, digital, analog) show boost in heatingcurve fix suspend on roomsetpoint in override HTTP endpoint /set OT bypass via MQTT
2026-03-10 fix ERCs & DRCs add TVS diodes to DQ & DI
2026-03-11 fix enable slave
2026-03-11 update README, add images
2026-03-11 supend below min. flow adjustable suspend offset
2026-03-12 fix flame ratio sensor
2026-03-12 add fiducals
2026-03-15 add 4 point curve
    add class for math logic
    add class for math logic
    add mapping
    add smooth steps
    fix offset
    fix debug compile
2026-03-15 changed: implementation to cpp
2026-03-15 changed: english comments
2026-03-15 change: move all heatconfig stuff to heatinglogic
2026-03-15 Removed retLimit (Return Limit) logic.
    Curve calculation lowers supply temperature if return temperature exceeds threshold.
    Potential future feature (condensing boiler optimization).
2026-03-15 add description
2026-03-15 use upstream master remove adaptiveMinFlow
2026-03-15 removed merge issue and warnings
2026-03-15 mirror fixes
2026-03-15 added 6 point curve
2026-03-16 add heatingcurve class for multipoint curve
2026-03-16 feature: multipoint curve mode
2026-03-16 serverside clamp validation
2026-03-16 add lowpass to Sensor class
2026-03-18 responsive webUI
2026-03-18 add responsive areas
2026-03-18 keep sensor values on reconfig
2026-03-18 add configuration for return temp
2026-03-19 add return temp limit to webUI
2026-03-19 show return limit in graph refactoring
2026-03-25 add flow return limit add config backup & restore HA secure value templates HA add mode state to climate controls HA add state to switch controls
2026-03-26 refactoring
2026-03-27 fix select source fields add label when dragging curve move neighbor points when dragging curve fix override logic refactoring
2026-03-30 build html.h before every build refactoring change multipoint clipping webUI export control CH override seperately for on and flow move flamestats to dedicated class
2026-03-30 add markings for loopback test
2026-03-30 update roomsetpoint immediately
2026-04-03 add actions for HA climate controls refactoring add html minifier
2026-04-04 fix room compensation clean up
2026-04-05 fix otMode setting fix input text settings
2026-04-05 add build.yml
2026-04-05 move workflow
2026-04-05 add submodules to build
2026-04-05 fix include
2026-04-05 add release to workflow
2026-04-05 fix slave enable
2026-04-05 create tag before release
2026-04-05 add build permission reload webUI on firmware change
2026-04-06 fix update buttons move wificlient
2026-04-07 adjust bounds for outside temperature
2026-04-08 build on new version
2026-04-10 clean up update via otthing server
2026-04-11 add toast messages remove HTP update
2026-04-11 prerelease
2026-04-12 improve build
2026-04-12 eyecandy
2026-04-12 fix default mode move production to own python file
2026-04-12 update build scripts
2026-04-12 install minify on build
2026-04-12 cleanup
2026-04-12 fix build
2026-04-12 fix minify
2026-04-12 fix build scripts
2026-04-13 fix adding marker eye candy
2026-04-13 increase status XHR timeout eye candy
2026-04-14 add infoboxes
2026-04-14 fix loopback mode on unprogrammed devices enhanced production script
2026-04-18 fix min. suspend add infoboxes
2026-04-18 fix infobox
2026-04-19 add last on time to webUI report success of set member ID
2026-04-19 fix 1w address selects
2026-04-20 make production faster increase version
2026-04-27 fix HA warnings
2026-05-01 filter invalid TSet values and correct OpenTherm f8.8 temperature decoding
2026-05-01 remove obsolete comment restart status update
2026-05-01 update productionhelper
2026-05-02 fix: clip negative TSet values from slave instead of ignoring them
2026-05-03 configurable hero cards
2026-05-03 fix: suppress CH enable when heating curve falls below flowMin
2026-05-03 suspend on flow below outside temp
2026-05-03 change label
2026-05-05 fix outsideTemp > roomset in heating curve
2026-05-05 fix sensorstatus for smoothed sensors
2026-05-05 expose summerMode & DHWblocking to home assistant
2026-05-06 announce config URL in HA
2026-05-07 fix warning
2026-05-07 fix cloaking with many slave values
2026-05-09 add request to low power
2026-05-13 set low flow temp on CH off
2026-05-14 add 500 ms request delay for tests
2026-05-20 configurable OT master delay
2026-06-02 HA versions -> diagnostic Fix CH 2 init
2026-06-02 refactor aux CH control
2026-06-02 Migrate to KiCad 10
2026-06-04 add more control cards to mock remove DHW lamp when no DHW present add scheduler
2026-06-04 exclude history
2026-06-04 add option for not sending DHW temp
2026-06-07 add compression for webUI and trend graph add timer mode
2026-06-10 pimp UI design improve production script
2026-06-20 add credentials for webUI
2026-06-20 update KiCad libraries
